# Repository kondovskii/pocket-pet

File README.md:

# Pocket Pet

Battery-powered handheld virtual pet on a custom 2-layer PCB. STM32L433,
FreeRTOS, hand-written SSD1306 driver, wake-on-motion.

**Status:** working. Board assembled and running the full firmware — display,
accelerometer, buttons, and battery power all verified on the custom hardware.

## Why this project

Built to close four specific gaps: custom PCB design, bare-metal ARM
programming, RTOS usage, and datasheet-level driver work. Every part was chosen
and every driver written from the datasheet rather than pulled from a library,
so that each decision is defensible.

## Hardware

| Block | Part | Notes |
|---|---|---|
| MCU | STM32L433CCT6 (LQFP-48) | Cortex-M4F, 256K flash, low-power STOP2 modes |
| Charger | MCP73831 | ~196 mA charge current (R_PROG = 5.1 k) |
| Regulator | MCP1700-3302 | 3.3 V LDO, low quiescent current |
| Input | USB-C, charge only | 5.1 k CC1/CC2 pull-downs for correct sink advertisement |
| Display | SSD1306 128x64, SPI | Hand-written driver, no vendor library |
| Motion | LIS3DH, I2C | Hand-written driver; soldered direct, isolatable via R6 |
| Battery | 500 mAh LiPo | JST-PH |

2-layer FR4, designed in KiCad, fabricated by JLCPCB.

## Design decisions

**MSI at 32 MHz, not HSI16, not 80 MHz.** MSI is the oscillator the L4 wakes on
coming out of STOP mode, and it can be trimmed against an LSE crystal. 32 MHz
was chosen over the 80 MHz maximum because the workload — a 128x64 display
refresh and an accelerometer read — does not need it, and lower active current
is free. The power story for a battery device is duty cycle (STOP2 at roughly
1 uA versus milliamps awake), not clock rate.

**USB-C is charge-only.** No USB data. The 5.1 k pull-downs on CC1 and CC2 are
what make a charger treat the board as a valid sink; without them a compliant
USB-C supply provides no VBUS at all. Programming and debug go over SWD, which
keeps the firmware simpler and the BOM smaller.

**0 ohm jumpers on the peripheral rails.** R5 and R6 sit in series with the
display and accelerometer supplies so either can be cut to measure that
peripheral's current draw in isolation, or to remove it from the picture while
debugging.

**I2C pull-ups fitted but not populated.** R7 and R8 are marked DNP because the
LIS3DH module carries its own. Measured at 10 k, which is weak for 400 kHz on
a board with no ground plane, so the bus runs at 100 kHz — the workload is
roughly 60 bytes per second, so there is nothing to gain from the higher rate
and the slower edges have four times the rise-time margin.

**Peripherals soldered directly.** The original plan was female headers so
modules could be swapped. They were dropped because SW1, the power switch, is
surface-mounted flat to the board and cannot rise with them — sockets would
have left it recessed roughly 8.5 mm below the display plane and complicated
the enclosure. The 0 ohm rail jumpers (R5, R6) preserve the debugging benefit:
either peripheral can be isolated or current-measured by lifting one resistor.

**SWD broken out to a 6-pin header** with SWDIO, SWCLK, SWO, NRST, 3V3 and GND,
in ST-Link pin order.

## Display driver

Written from the SSD1306 datasheet rather than pulled from a library: SPI
transport with manual DC and CS control, the full initialisation sequence, a
1024-byte framebuffer, Bresenham line drawing, and a 5x7 column-major font.

**Draw to RAM, flush once.** Every primitive writes to the framebuffer and
nothing reaches the panel until `ssd1306_update_screen()`. Frames appear whole
rather than building up visibly, and the flush is a single 1024-byte SPI burst
instead of hundreds of small transfers.

**The font is column-major** because that matches the controller's own vertical
byte layout, so rendering a glyph is a single bit test per pixel with no
transposition.

**Clipping lives in one place.** Only `ssd1306_draw_pixel()` bounds-checks;
lines, rectangles and text all inherit it. One guard to get right instead of
six, and no way for them to disagree.

**Validated on a NUCLEO-L432KC with a 7-pin SPI module before the custom boards
arrived**, so that display bring-up and board bring-up could be debugged
independently. A blank screen on the custom board now means a hardware fault,
not an unproven driver.

## Motion driver

I2C driver for the LIS3DH, written from the datasheet: register map, burst
reads, and a WHO_AM_I identity check that fails loudly rather than returning
plausible garbage.

**Auto-increment must be requested explicitly.** Bit 7 of the register address
tells the part to advance its internal pointer across a burst. Without it,
reading six bytes from `OUT_X_L` returns the same register six times — all
three axes identical, which looks exactly like a dead sensor rather than a
protocol mistake.

**Block Data Update is enabled** so the part cannot refresh an output register
pair between the read of the low byte and the high byte. Without it, occasional
samples are the low half of one reading stitched to the high half of the next.

**Signed arithmetic shift for the 12-bit values.** Output is left-justified
16-bit; high-resolution mode makes only the top 12 bits meaningful. Shifting a
signed type sign-extends and preserves negative readings, where the same shift
on an unsigned type would turn -1 into 4095.

**The I2C address depends on the board, not the chip.** On the Nucleo bench
wiring SA0 and CS float, and the module's own strapping gives 0x19. On the
custom board J6 ties SA0 to ground and CS to 3V3, giving 0x18. The address
therefore lives in `pocket_pet_pins.h` behind a board selector rather than in
the driver, because it is a board fact.

## RTOS architecture

Three tasks, no shared state.

    inputTask    polls and debounces the buttons, detects shake, publishes events
    petTask      owns the pet state, applies events, ticks it forward once a second
    displayTask  redraws at 8 fps, taking a new state when one is available

Tasks communicate only through queues, and the pet state is passed **by value**
rather than by pointer — each task works on its own copy, so there is no shared
memory, no mutex, and no race to get wrong.

The two queues have deliberately different depths. The state queue is depth 1
because the display only ever cares about the newest state; a deeper one would
just mean rendering stale frames. The event queue is depth 4 because a dropped
button press is a bug, where a dropped frame is not.

**Input is edge-triggered, not level.** A press registers on the
released-to-pressed transition, so holding a button feeds the pet once rather
than continuously.

**The display task runs on a timer, not on the queue.** It was originally
blocked on `osWaitForever`, which meant it only redrew when the pet state
changed — once a second, far too slow for animation. It now wakes every 125 ms
and takes a new state if one is waiting, so rendering rate and simulation rate
are decoupled.

## Game design

Three stats decay on separate timescales: hunger fastest, then mood, then
energy. Any stat reaching zero starts a two-minute distress countdown with a
visible warning; ignoring it kills the pet. The countdown exists so that death
is a consequence of ignoring something, not a surprise.

**The lowest stat decides the pet's expression**, so it looks as bad as its
worst problem rather than averaging out and hiding the thing the player needs
to notice.

**Two buttons, four actions.** Left feeds. Right plays on a short press and
toggles sleep on a one-second hold. Shaking the board is a third input,
detected by comparing squared acceleration magnitude against a threshold —
squared, so the comparison needs no square root and no floating point.

**Sleep is the only way to recover energy**, and playing costs it, so the
stats interact rather than being three independent bars.

**Actions trigger a two-second reaction animation.** This confirms the press
registered, and gives the less-frequently-seen animations a reason to exist —
most moods map to slow-moving stats you rarely watch change.

## Known issues (v1.0)

Found during a design review after the boards were already at fab. Documented
rather than hidden — these are the v1.1 fix list.

- **No ground pour on either layer.** Every return path is a narrow trace, which
  raises loop inductance and leaves the MCP73831 with no thermal copper. Expect
  the charger to run warm and possibly fold back current.
- **No reverse-polarity protection on the battery input.** A backwards cell would
  destroy the charger. Mitigated only by silkscreen.
- **No load-sharing.** The load hangs off the battery node, so the board is not
  designed to run from USB with no cell installed.
- **No battery voltage sensing.** No way to report state of charge. A divider to
  an ADC pin is the fix.
- **Decoupling placement is loose** — several caps sit millimetres from the pins
  they serve, which without a plane makes them largely ineffective.
- **STAT pin unconnected**, so there is no charge indicator LED.
- Silkscreen needs a cleanup pass: unannotated mounting holes, overlapping value
  text, no pin-1 markers or header labels.
- **Cold joints on the USB-C VBUS pin killed the first assembly attempt.**
  VBUS and GND have multiple redundant pins; CC1 and CC2 have exactly one
  each, so a single bad joint silently kills power negotiation with no other
  symptom. Worth probing CC-to-GND for 5.1 k before troubleshooting anything
  else.
- **The Nucleo-32's ST-Link cannot program an external target.** Unlike
  Nucleo-64 and -144, it has no break-out SWD connector — the debugger is
  hardwired to the on-board MCU, and CN2 is reserved for reflashing the
  ST-Link's own processor. A standalone ST-Link V2 is required. Worth knowing
  before planning a bring-up around a Nucleo.
- Debug sessions corrupt I²C. With SWD active, lis3dh_init() fails intermittently; disconnecting the debugger makes it reliable.  SWDIO and SWCLK run adjacent to the I²C lines with no ground plane between them. Worth knowing that on this board a peripheral failure seen under the debugger may not be a real failure.
- **Task stacks were too small, and the first fix silently undid itself.**
  The display task ran on CubeMX's default 512 bytes, which `snprintf`, newlib
  reentrancy and the scaled bitmap blit comfortably exceed. The symptom was a
  HardFault minutes after boot, triggered by bursts of input, with nothing
  obviously stack-related in the trace. It was fixed once by hand, but the
  default task's stack size lives in generated code outside the USER CODE
  markers, so the next CubeMX regeneration quietly reverted it. Now set in the
  .ioc at 2 KB per task, with configCHECK_FOR_STACK_OVERFLOW enabled so any
  future overflow halts in a named hook rather than surfacing as an unrelated
  fault.
- **The battery arrived with its JST housing wired backwards.** With no
  reverse-polarity protection on v1.0 that would have destroyed the charger.
  Worth measuring cell polarity against the board's silkscreen before every
  first connection.
- **Cheap USB-C charger modules often omit the CC pull-downs.** A TP4056
  module appeared dead on a compliant USB-C supply because it never
  negotiated; it worked immediately from a legacy USB-A source. The same
  5.1 k resistors this board fits as R2/R3.
  - **Changing I2C speed in CubeMX did not update the generated timing register.**
  The .ioc read Standard Mode while `MX_I2C1_Init()` still carried the Fast
  Mode timing value, so the bus ran at 400 kHz regardless. With 10 k pull-ups
  and no ground plane that was marginal, and produced intermittent LIS3DH
  failures that looked like a driver or wiring fault. Toggling the mode and
  disabling custom timing both failed to force a recalculation; the value had
  to be entered by hand. Verify `hi2c1.Init.Timing` in i2c.c after any speed
  change rather than trusting the .ioc.

## Repository layout

    hardware/pocket-pet/     KiCad project, fab outputs under fab/
    firmware/pocket-pet-nucleo/   Bring-up project, NUCLEO-L432KC
    firmware/pocket-pet-board/    Custom board project
    docs/                    Schematic PDF, renders, BOM

## Building the firmware

Requires STM32CubeIDE. Import the project with "Copy projects into workspace"
unchecked so the IDE edits the repo in place; keep the workspace outside the
repository. The .ioc file is the source of truth for pin configuration — if you
change pins, regenerate from CubeMX rather than editing generated code.
Any value in generated code outside the USER CODE markers — task stack sizes,
heap size, peripheral settings — must be changed in the .ioc, not the source.
Hand edits there are overwritten on the next regeneration without warning.

## Sprites

Sprite data is not included in this repository. The bunny animations are from
[VegaJourney's 32x32 Bunny pack](https://toffeecraft.itch.io/bunny-pixel-animations) (licence permits use but
not redistribution), converted to 1-bit bitmaps.

To build: copy `firmware/common/pet_sprites.h.template` to `pet_sprites.h`
and supply your own sprite arrays. Any 1-bit bitmap works — 
`ssd1306_draw_bitmap()` takes row-major, MSB-first data, which is what
[image2cpp](https://javl.github.io/image2cpp/) produces with horizontal
orientation selected.

## License

MIT

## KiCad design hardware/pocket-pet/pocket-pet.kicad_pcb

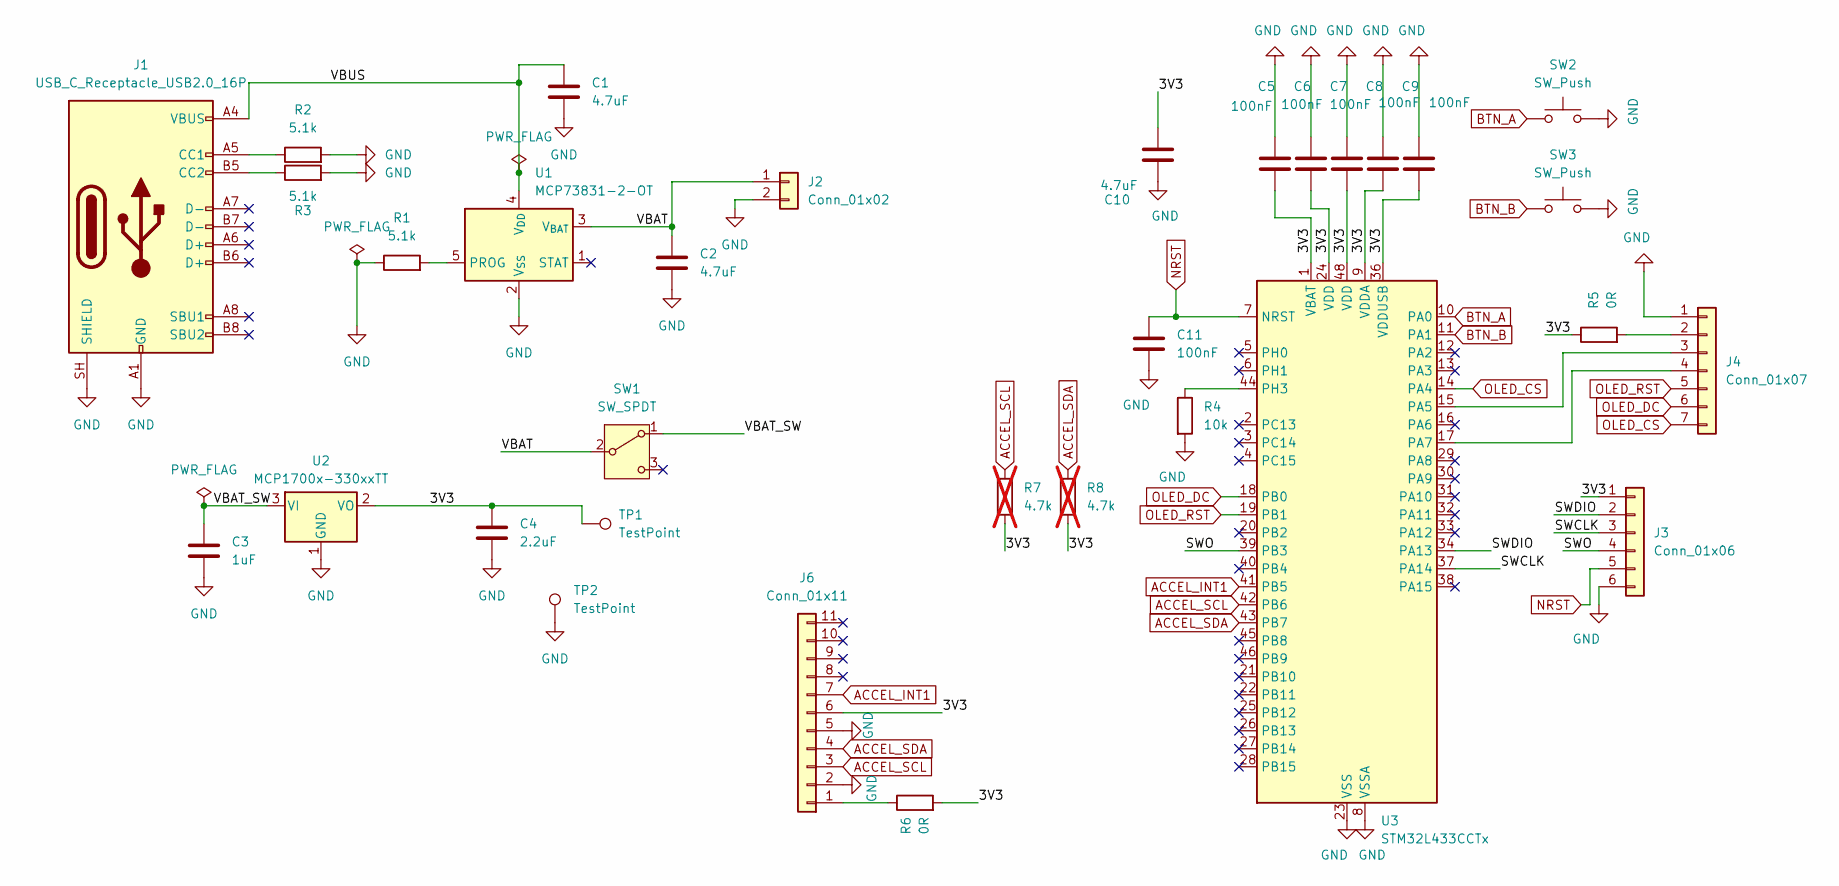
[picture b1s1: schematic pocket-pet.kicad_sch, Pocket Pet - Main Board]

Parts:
C1, C2, C10: 4.7uF; C_0805_2012Metric_Pad1.18x1.45mm_HandSolder
C3: 1uF; C_0805_2012Metric_Pad1.18x1.45mm_HandSolder
C4: 2.2uF; C_0805_2012Metric_Pad1.18x1.45mm_HandSolder
C5, C6, C7, C8, C9, C11: 100nF; C_0805_2012Metric_Pad1.18x1.45mm_HandSolder
J1: USB_C_Receptacle_USB2.0_16P; USB_C_Receptacle_HRO_TYPE-C-31-M-12
J2: Conn_01x02; JST_PH_S2B-PH-K_1x02_P2.00mm_Horizontal
J3: Conn_01x06; PinHeader_1x06_P2.54mm_Vertical
J4: Conn_01x07; PinHeader_1x07_P2.54mm_Vertical
J6: Conn_01x11; PinHeader_1x11_P2.54mm_Vertical
R1, R2, R3: 5.1k; R_0805_2012Metric_Pad1.20x1.40mm_HandSolder
R4: 10k; R_0805_2012Metric_Pad1.20x1.40mm_HandSolder
R5, R6: 0R; R_0805_2012Metric_Pad1.20x1.40mm_HandSolder
R7, R8: 4.7k; R_0805_2012Metric_Pad1.20x1.40mm_HandSolder; not fitted
SW1: SW_SPDT; SW_Slide_SS12D00G3_P2.5mm
SW2, SW3: SW_Push; SW_PUSH_6mm
TP1: TestPoint; TestPoint_Pad_D1.5mm
TP2: TestPoint; TestPoint_THTPad_D2.0mm_Drill1.0mm
U1: MCP73831-2-OT; SOT-23-5
U2: MCP1700x-330xxTT; SOT-23
U3: STM32L433CCTx; LQFP-48_7x7mm_P0.5mm

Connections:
/3V3: C4.1, C5.1, C6.1, C7.1, C8.1, C9.1, C10.1, J3.1, J6.6, R5.1, R6.2, R7.2, R8.2, TP1.1 (1_1), U2.2 (VO), U3.1 (VBAT), U3.9 (VDDA), U3.24 (VDD), U3.36 (VDDUSB), U3.48 (VDD)
/SWCLK: J3.3, U3.37 (PA14)
/SWDIO: J3.2, U3.34 (PA13)
/SWO: J3.4, U3.39 (PB3)
/VBAT: C2.1, J2.1, SW1.2 (B), U1.3 (V_{BAT})
/VBAT_SW: C3.1, SW1.1 (A), U2.3 (VI)
/VBUS: C1.1, J1.A4 (VBUS), J1.A9 (VBUS), J1.B4 (VBUS), J1.B9 (VBUS), U1.4 (V_{DD})
ACCEL_INT1: J6.7, U3.41 (PB5)
ACCEL_SCL: J6.3, R7.1, U3.42 (PB6)
ACCEL_SDA: J6.4, R8.1, U3.43 (PB7)
BTN_A: SW2.1, U3.10 (PA0)
BTN_B: SW3.1, U3.11 (PA1)
GND: C1.2, C2.2, C3.2, C4.2, C5.2, C6.2, C7.2, C8.2, C9.2, C10.2, C11.2, J1.A1 (GND), J1.A12 (GND), J1.B1 (GND), J1.B12 (GND), J1.SH (SHIELD), J2.2, J3.6, J4.1, J6.2, J6.5, R1.1, R2.2, R3.2, R4.2, SW2.2, SW3.2, TP2.1 (1_1), U1.2 (V_{SS}), U2.1 (GND), U3.8 (VSSA), U3.23 (VSS), U3.35 (VSS), U3.47 (VSS)
NRST: C11.1, J3.5, U3.7 (NRST)
unnamed: J1.A5 (CC1), R2.1
unnamed: J1.B5 (CC2), R3.1
unnamed: J4.2, R5.2
unnamed: J4.3, U3.15 (PA5)
unnamed: J4.4, U3.17 (PA7)
unnamed: J6.1, R6.1
unnamed: R1.2, U1.5 (PROG)
unnamed: R4.1, U3.44 (PH3)
OLED_CS: J4.7, U3.14 (PA4)
OLED_DC: J4.6, U3.18 (PB0)
OLED_RST: J4.5, U3.19 (PB1)

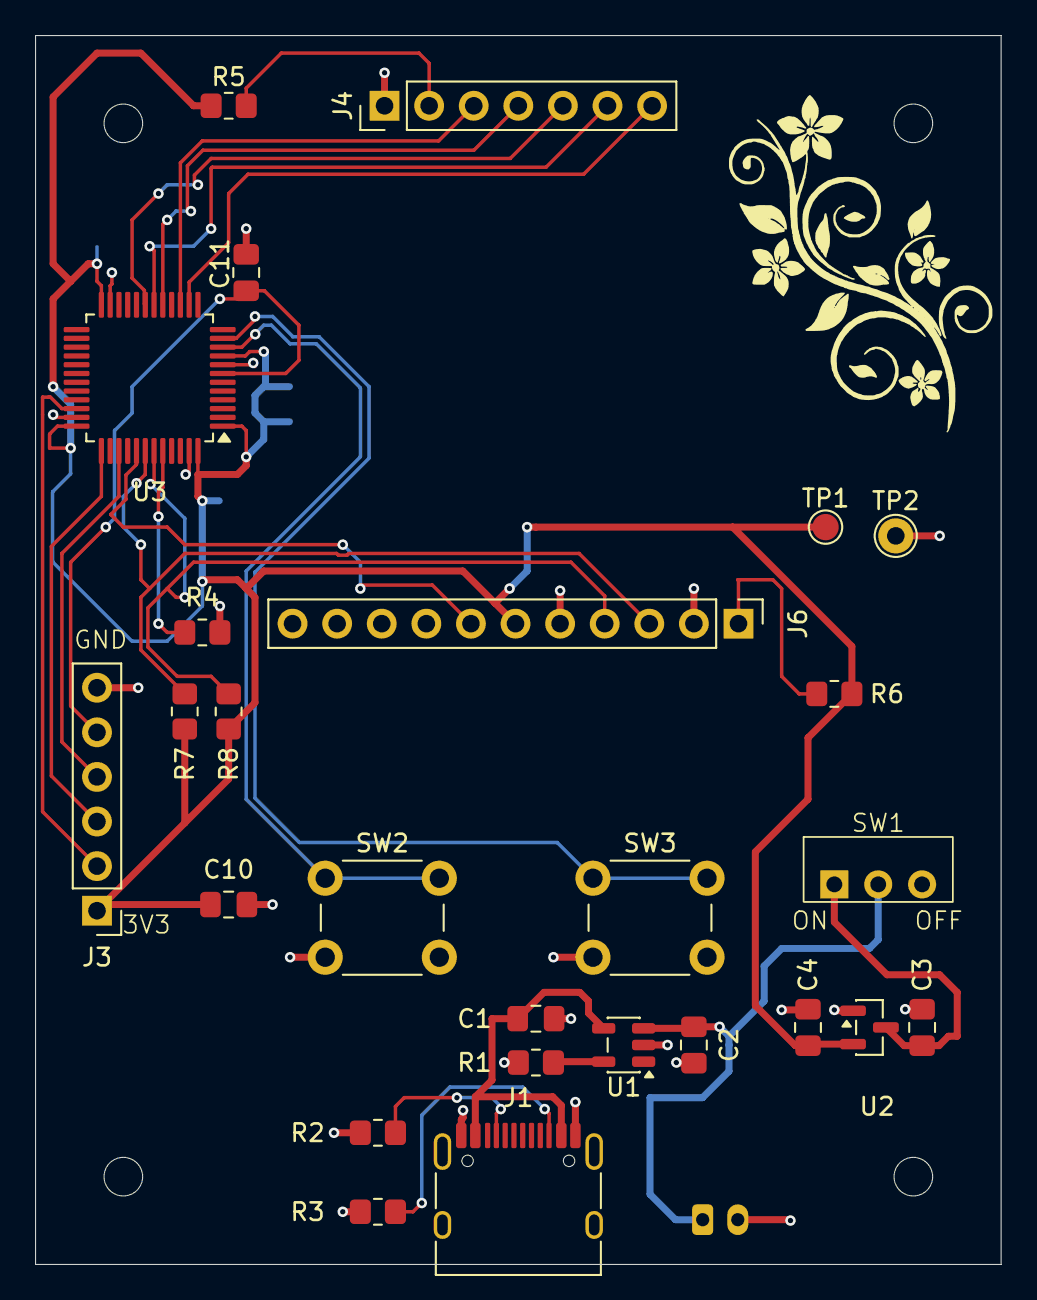
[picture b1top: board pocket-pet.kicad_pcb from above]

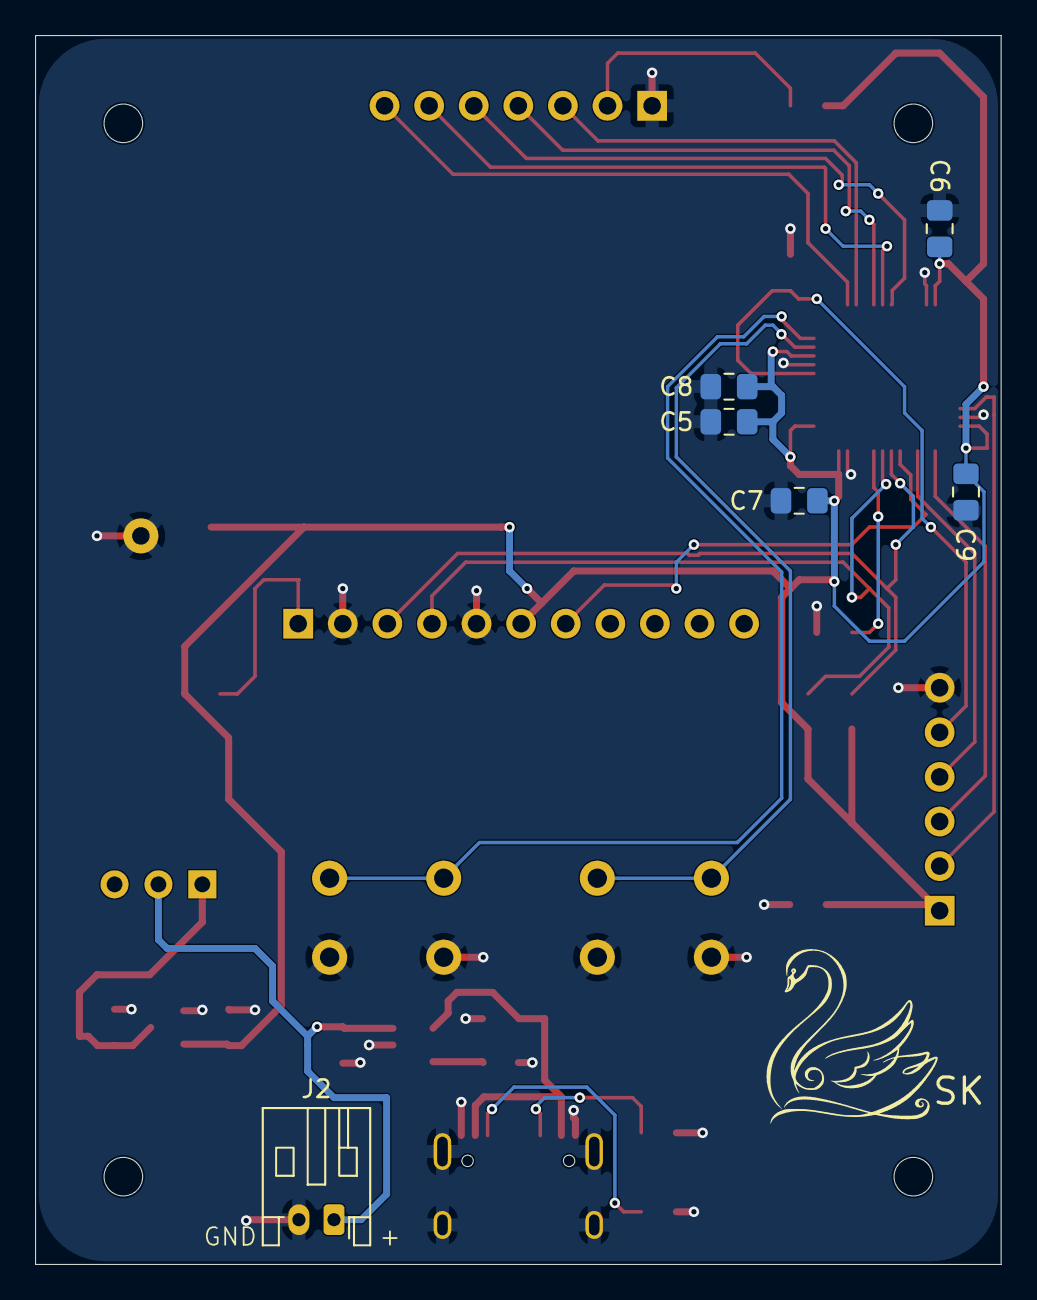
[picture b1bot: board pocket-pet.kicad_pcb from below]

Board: 2 copper layers, 55.0 x 70.0 mm, 32 parts (6 on the bottom side), 25 nets.

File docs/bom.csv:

Reference,Qty,Value,LCSC,DNP,Exclude from BOM,Exclude from Board,Exclude from Simulation,Exclude from Position Files,Footprint,Datasheet
"C1,C2,C10",3,4.7uF,C1779,,,,,${EXCLUDE_FROM_POS_FILES},Capacitor_SMD:C_0805_2012Metric_Pad1.18x1.45mm_HandSolder,
C3,1,1uF,C28323,,,,,${EXCLUDE_FROM_POS_FILES},Capacitor_SMD:C_0805_2012Metric_Pad1.18x1.45mm_HandSolder,
C4,1,2.2uF,C377773,,,,,${EXCLUDE_FROM_POS_FILES},Capacitor_SMD:C_0805_2012Metric_Pad1.18x1.45mm_HandSolder,
"C5,C6,C7,C8,C9,C11",6,100nF,C49678,,,,,${EXCLUDE_FROM_POS_FILES},Capacitor_SMD:C_0805_2012Metric_Pad1.18x1.45mm_HandSolder,
J1,1,USB_C_Receptacle_USB2.0_16P,C165948,,,,,${EXCLUDE_FROM_POS_FILES},Connector_USB:USB_C_Receptacle_HRO_TYPE-C-31-M-12,https://www.usb.org/sites/default/files/documents/usb_type-c.zip
J2,1,Conn_01x02,C157932,,,,,${EXCLUDE_FROM_POS_FILES},Connector_JST:JST_PH_S2B-PH-K_1x02_P2.00mm_Horizontal,
J3,1,Conn_01x06,,,,,,${EXCLUDE_FROM_POS_FILES},Connector_PinHeader_2.54mm:PinHeader_1x06_P2.54mm_Vertical,
J4,1,Conn_01x07,,,,,,${EXCLUDE_FROM_POS_FILES},Connector_PinHeader_2.54mm:PinHeader_1x07_P2.54mm_Vertical,
J6,1,Conn_01x11,,,,,,${EXCLUDE_FROM_POS_FILES},Connector_PinHeader_2.54mm:PinHeader_1x11_P2.54mm_Vertical,
"R1,R2,R3",3,5.1k,C27834,,,,,${EXCLUDE_FROM_POS_FILES},Resistor_SMD:R_0805_2012Metric_Pad1.20x1.40mm_HandSolder,
R4,1,10k,C2907219,,,,,${EXCLUDE_FROM_POS_FILES},Resistor_SMD:R_0805_2012Metric_Pad1.20x1.40mm_HandSolder,
"R5,R6",2,0R,C17477,,,,,${EXCLUDE_FROM_POS_FILES},Resistor_SMD:R_0805_2012Metric_Pad1.20x1.40mm_HandSolder,
"R7,R8",2,4.7k,C2907264,DNP,,,,${EXCLUDE_FROM_POS_FILES},Resistor_SMD:R_0805_2012Metric_Pad1.20x1.40mm_HandSolder,
SW1,1,SW_SPDT,,,,,,${EXCLUDE_FROM_POS_FILES},pocket-pet:SW_Slide_SS12D00G3_P2.5mm,
"SW2,SW3",2,SW_Push,,,,,,${EXCLUDE_FROM_POS_FILES},Button_Switch_THT:SW_PUSH_6mm,
TP1,1,TestPoint,,,,,,${EXCLUDE_FROM_POS_FILES},TestPoint:TestPoint_Pad_D1.5mm,
TP2,1,TestPoint,,,,,,${EXCLUDE_FROM_POS_FILES},TestPoint:TestPoint_THTPad_D2.0mm_Drill1.0mm,
U1,1,MCP73831-2-OT,C424093,,,,,${EXCLUDE_FROM_POS_FILES},Package_TO_SOT_SMD:SOT-23-5,http://ww1.microchip.com/downloads/en/DeviceDoc/20001984g.pdf
U2,1,MCP1700x-330xxTT,C39051,,,,,${EXCLUDE_FROM_POS_FILES},Package_TO_SOT_SMD:SOT-23,http://ww1.microchip.com/downloads/en/DeviceDoc/20001826D.pdf
U3,1,STM32L433CCTx,C110061,,,,,${EXCLUDE_FROM_POS_FILES},Package_QFP:LQFP-48_7x7mm_P0.5mm,https://www.st.com/resource/en/datasheet/stm32l433cc.pdf

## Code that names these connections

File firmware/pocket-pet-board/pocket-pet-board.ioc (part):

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Mcu.Name=STM32L433C(B-C)Tx
Mcu.Package=LQFP48
Mcu.UserName=STM32L433CCTx
PA0.GPIOParameters=GPIO_PuPd,GPIO_Label
PA0.GPIO_Label=BTN_A
PA0.GPIO_PuPd=GPIO_PULLUP
PA0.Signal=GPIO_Input
PA1.GPIOParameters=GPIO_PuPd,GPIO_Label
PA1.GPIO_Label=BTN_B
PA1.GPIO_PuPd=GPIO_PULLUP
PA1.Signal=GPIO_Input
PA13\ (JTMS-SWDIO).Mode=Trace_Asynchronous_SW
PA13\ (JTMS-SWDIO).Signal=SYS_JTMS-SWDIO
PA14\ (JTCK-SWCLK).Mode=Trace_Asynchronous_SW
PA14\ (JTCK-SWCLK).Signal=SYS_JTCK-SWCLK
PA4.GPIOParameters=PinState,GPIO_Label
PA4.GPIO_Label=OLED_CS
PA4.PinState=GPIO_PIN_SET
PA4.Signal=GPIO_Output
PA5.Mode=TX_Only_Simplex_Unidirect_Master
PA5.Signal=SPI1_SCK
PA7.Mode=TX_Only_Simplex_Unidirect_Master
PA7.Signal=SPI1_MOSI
PB0.GPIOParameters=GPIO_Label
PB0.GPIO_Label=OLED_DC
PB0.Signal=GPIO_Output
PB1.GPIOParameters=PinState,GPIO_Label
PB1.GPIO_Label=OLED_RST
PB1.PinState=GPIO_PIN_SET
PB1.Signal=GPIO_Output
PB3\ (JTDO-TRACESWO).Mode=Trace_Asynchronous_SW
PB3\ (JTDO-TRACESWO).Signal=SYS_JTDO-SWO
PB5.GPIOParameters=GPIO_Label
PB5.GPIO_Label=ACCEL_INT1
PB5.Signal=GPIO_Input
PB6.GPIOParameters=GPIO_Label
PB6.GPIO_Label=ACCEL_SCL
PB6.Mode=I2C
PB6.Signal=I2C1_SCL
PB7.GPIOParameters=GPIO_Label
PB7.GPIO_Label=ACCEL_SDA
PB7.Mode=I2C
PB7.Signal=I2C1_SDA
RCC.HSE_VALUE=8000000
RCC.SYSCLKFreq_VALUE=32000000
RCC.SYSCLKSource=RCC_SYSCLKSOURCE_PLLCLK
board=custom
